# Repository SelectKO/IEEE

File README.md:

# IEEE
Projeto teste para minicurso de Git

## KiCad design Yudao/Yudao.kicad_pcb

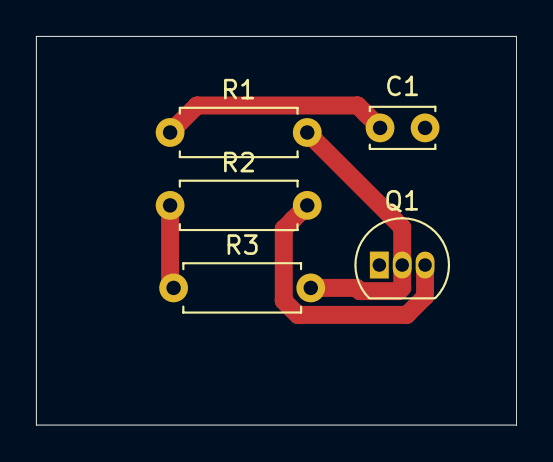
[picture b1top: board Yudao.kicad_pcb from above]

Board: 2 copper layers, 26.7 x 21.6 mm, 5 parts (0 on the bottom side), 4 nets.

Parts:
C1: 20nF; C_Disc_D3.4mm_W2.1mm_P2.50mm
Q1: BC548; TO-92_Inline
R1: 1k; R_Axial_DIN0207_L6.3mm_D2.5mm_P7.62mm_Horizontal
R2: 10k; R_Axial_DIN0207_L6.3mm_D2.5mm_P7.62mm_Horizontal
R3: 510k; R_Axial_DIN0207_L6.3mm_D2.5mm_P7.62mm_Horizontal

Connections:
GND: R2.1, R3.1
unnamed: C1.1, R1.1
unnamed: Q1.2, R1.2, R3.2
unnamed: Q1.3, R2.2

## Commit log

2019-08-09 Esquema do circuito
    Foi adicionado o esquema do circuito no KiCad
2019-08-10 Selecionar footprints
    Footprints selecionadas
